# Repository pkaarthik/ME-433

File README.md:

# ME-433

This repo consists of assignments for the ME433 course at Northwestern University, offered in Spring 2021. Each of the individual folders has the submissions for those specific assignments (code, pictures and demo videos).

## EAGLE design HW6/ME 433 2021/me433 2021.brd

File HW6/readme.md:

**HW6**

In this assignment, I use Eagle CAD (free version) to design a circuit diagram, and it's PCB for the final project system in ME 433.

Note: Please find screenshots of the board, cropped for a more zoomed in view and a more full view. 

Note: The PololuDVR8835 uses a DIL-14 footprint despite not exactly matching the same footprint, since the pin spacing and column width of the DVR8835 matches a DIL14 footprint layout.

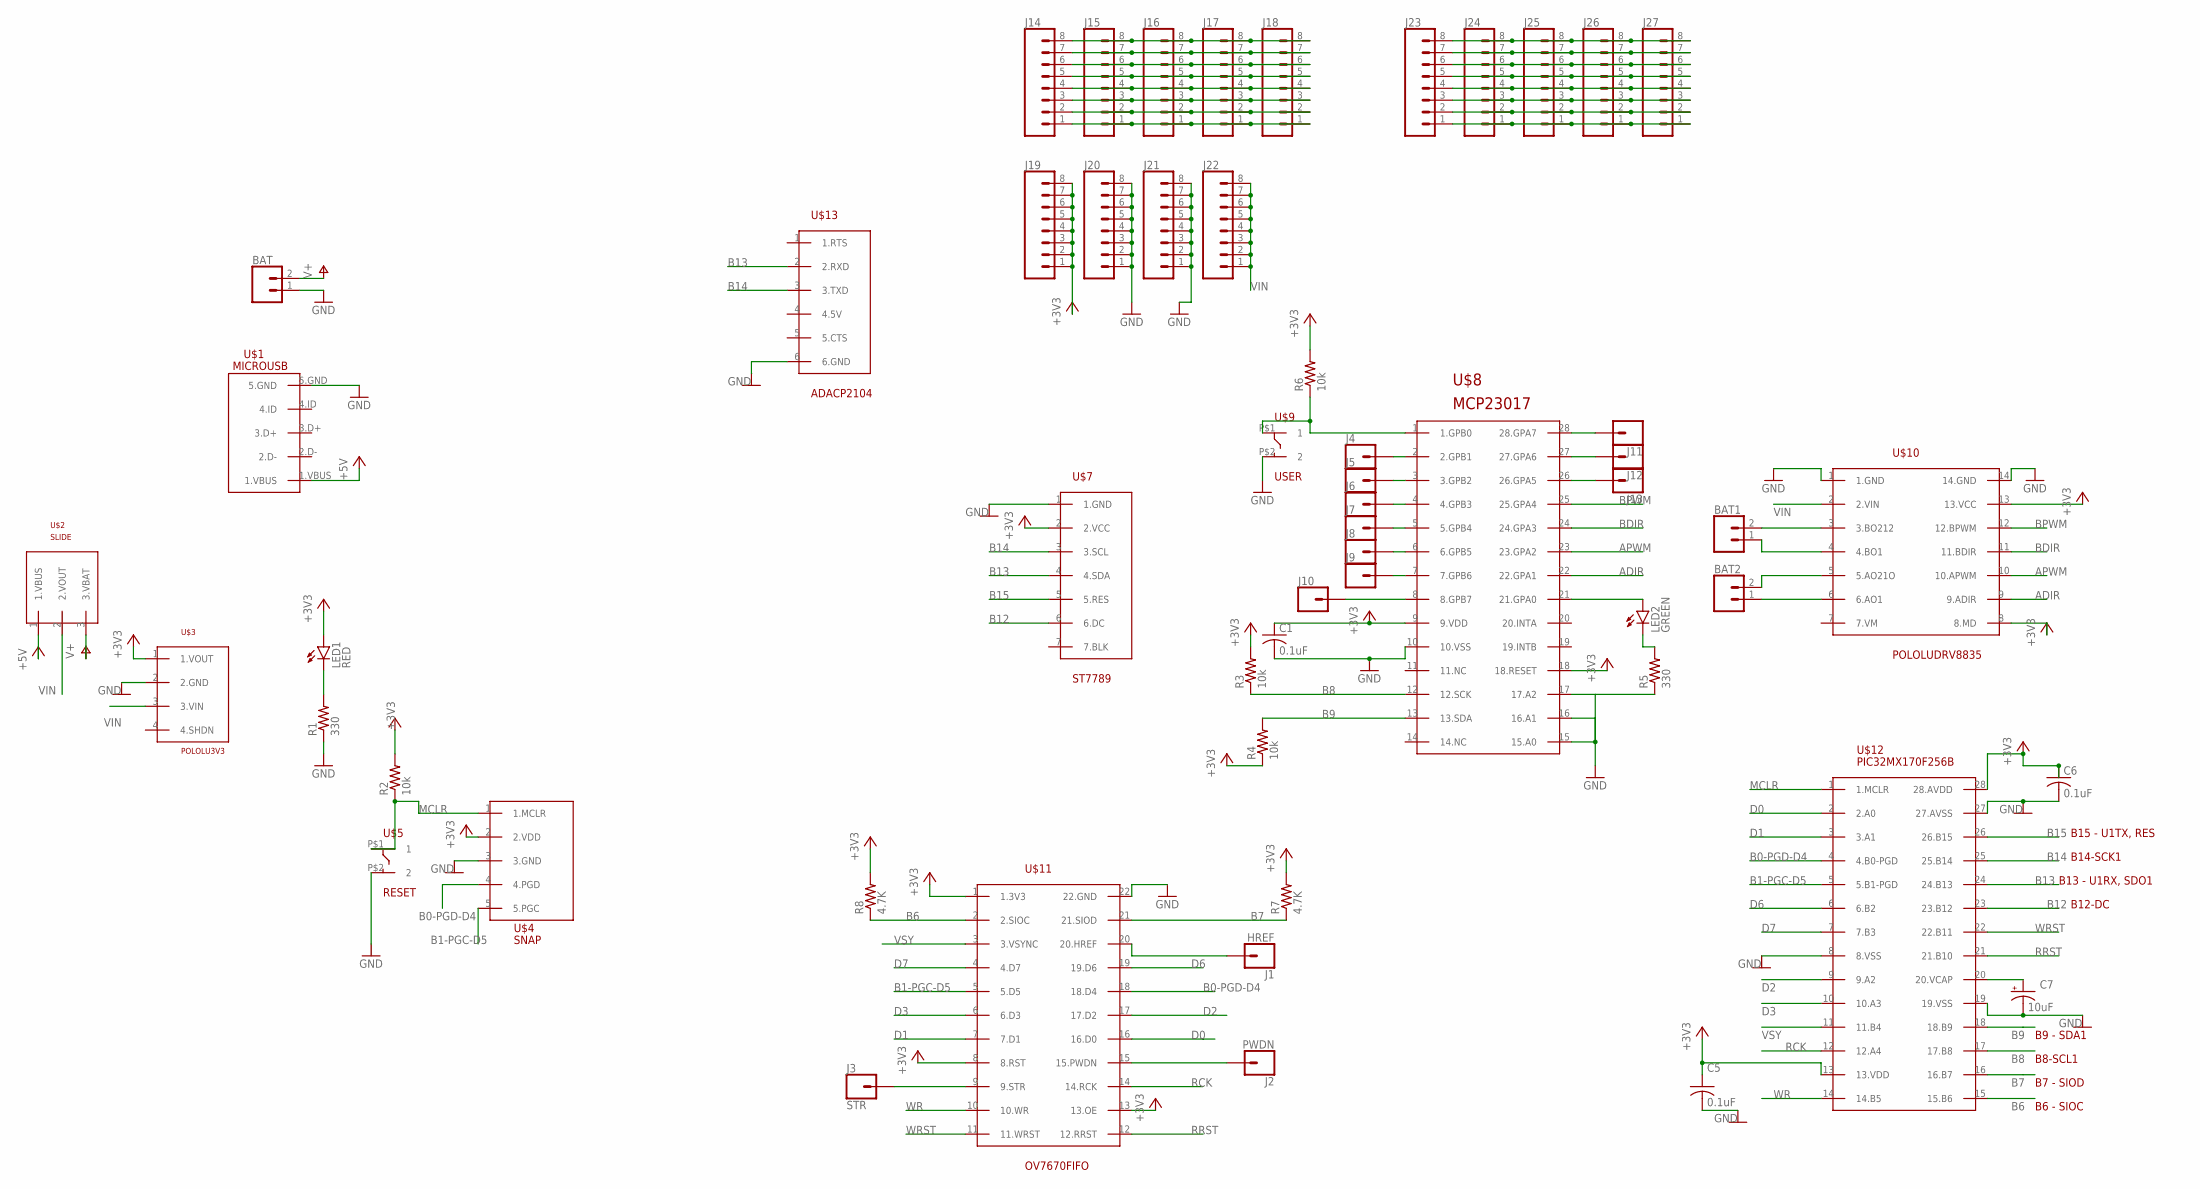
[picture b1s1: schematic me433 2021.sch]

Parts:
BAT, BAT1, BAT2: CONN_02; 1X02
C1, C5, C6: 0.1uF; C025-030X050
C7: 10uF; B45181B
J1: HREF; 1X01
J2: PWDN; 1X01
J3: STR; 1X01
J4, J5, J6, J7, J8, J9, J10, J11, J12, J13: CONN_01; 1X01
J14, J15, J16, J17, J18, J19, J20, J21, J22, J23, J24, J25, J26, J27: CONN_08"; 1X08
LED1: RED; LED3MM
LED2: GREEN; LED3MM
R1, R5: 330; 0207/10
R2, R3, R4, R6: 10k; 0207/10
R7, R8: 4.7K; 0207/10
U$1: MICROUSB
U$2: SLIDE
U$3: POLOLU3V3
U$4: SNAP
U$5: RESET; PUSH
U$7: ST7789
U$8: MCP23017; DIL28-3
U$9: USER; PUSH
U$10: POLOLUDRV8835; DIL14
U$11: OV7670FIFO
U$12: PIC32MX170F256B; DIL28-3
U$13: ADACP2104

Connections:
+3V3: C1.1, C5.1, C6.1, J19.1, J19.2, J19.3, J19.4, J19.5, J19.6, J19.7, J19.8, LED1.A, R2.2, R3.2, R4.1, R6.2, R7.2, R8.2, U$3.1 (1.VOUT), U$4.2 (2.VDD), U$7.2 (2.VCC), U$8.9 (9.VDD), U$8.18 (18.RESET), U$10.8 (8.MD), U$10.13 (13.VCC), U$11.1 (1.3V3), U$11.8 (8.RST), U$11.13 (13.OE), U$12.13 (13.VDD), U$12.28 (28.AVDD)
+5V: U$1.1.VBUS, U$2.1 (1.VBUS)
ADIR: U$8.22 (22.GPA1), U$10.9 (9.ADIR)
APWM: U$8.23 (23.GPA2), U$10.10 (10.APWM)
B0-PGD-D4: U$4.4 (4.PGD), U$11.18 (18.D4), U$12.4 (4.B0-PGD)
B1-PGC-D5: U$4.5 (5.PGC), U$11.5 (5.D5), U$12.5 (5.B1-PGD)
B6: R8.1, U$11.2 (2.SIOC), U$12.15 (15.B6)
B7: R7.1, U$11.21 (21.SIOD), U$12.16 (16.B7)
B8: R3.1, U$8.12 (12.SCK), U$12.17 (17.B8)
B9: R4.2, U$8.13 (13.SDA), U$12.18 (18.B9)
B12: U$7.6 (6.DC), U$12.23 (23.B12)
B13: U$7.4 (4.SDA), U$12.24 (24.B13), U$13.2 (2.RXD)
B14: U$7.3 (3.SCL), U$12.25 (25.B14), U$13.3 (3.TXD)
B15: U$7.5 (5.RES), U$12.26 (26.B15)
BDIR: U$8.24 (24.GPA3), U$10.11 (11.BDIR)
BPWM: U$8.25 (25.GPA4), U$10.12 (12.BPWM)
D0: U$11.16 (16.D0), U$12.2 (2.A0)
D1: U$11.7 (7.D1), U$12.3 (3.A1)
D2: U$11.17 (17.D2), U$12.9 (9.A2)
D3: U$11.6 (6.D3), U$12.10 (10.A3)
D6: U$11.19 (19.D6), U$12.6 (6.B2)
D7: U$11.4 (4.D7), U$12.7 (7.B3)
GND: BAT.1, C1.2, C5.2, C6.2, C7.-, J20.1, J20.2, J20.3, J20.4, J20.5, J20.6, J20.7, J20.8, J21.1, J21.2, J21.3, J21.4, J21.5, J21.6, J21.7, J21.8, R1.1, R5.1, U$1.5.GND, U$3.2 (2.GND), U$4.3 (3.GND), U$5.P$2 (2), U$7.1 (1.GND), U$8.10 (10.VSS), U$8.15 (15.A0), U$8.16 (16.A1), U$8.17 (17.A2), U$9.P$2 (2), U$10.1 (1.GND), U$10.14 (14.GND), U$11.22 (22.GND), U$12.8 (8.VSS), U$12.19 (19.VSS), U$12.27 (27.AVSS), U$13.6 (6.GND)
MCLR: R2.1, U$4.1 (1.MCLR), U$5.P$1 (1), U$12.1 (1.MCLR)
unnamed: LED1.K (C), R1.2
unnamed: J3.1, U$11.9 (9.STR)
unnamed: R6.1, U$8.1 (1.GPB0), U$9.P$1 (1)
unnamed: LED2.A, U$8.21 (21.GPA0)
unnamed: LED2.K (C), R5.2
unnamed: BAT1.2, U$10.3 (3.BO212)
unnamed: BAT1.1, U$10.4 (4.BO1)
unnamed: BAT2.2, U$10.5 (5.AO21O)
unnamed: BAT2.1, U$10.6 (6.AO1)
unnamed: J2.1, U$11.15 (15.PWDN)
unnamed: J1.1, U$11.20 (20.HREF)
unnamed: J4.1, U$8.2 (2.GPB1)
unnamed: J10.1, U$8.8 (8.GPB7)
unnamed: J5.1, U$8.3 (3.GPB2)
unnamed: J6.1, U$8.4 (4.GPB3)
unnamed: J7.1, U$8.5 (5.GPB4)
unnamed: C7.+, U$12.20 (20.VCAP)
unnamed: J8.1, U$8.6 (6.GPB5)
unnamed: J9.1, U$8.7 (7.GPB6)
unnamed: J11.1, U$8.28 (28.GPA7)
unnamed: J12.1, U$8.27 (27.GPA6)
unnamed: J13.1, U$8.26 (26.GPA5)
unnamed: J14.8, J15.8, J16.8, J17.8, J18.8
unnamed: J14.7, J15.7, J16.7, J17.7, J18.7
unnamed: J14.6, J15.6, J16.6, J17.6, J18.6
unnamed: J14.5, J15.5, J16.5, J17.5, J18.5
unnamed: J14.4, J15.4, J16.4, J17.4, J18.4
unnamed: J14.3, J15.3, J16.3, J17.3, J18.3
unnamed: J14.2, J15.2, J16.2, J17.2, J18.2
unnamed: J14.1, J15.1, J16.1, J17.1, J18.1
unnamed: J23.8, J24.8, J25.8, J26.8, J27.8
unnamed: J23.7, J24.7, J25.7, J26.7, J27.7
unnamed: J23.6, J24.6, J25.6, J26.6, J27.6
unnamed: J23.5, J24.5, J25.5, J26.5, J27.5
unnamed: J23.4, J24.4, J25.4, J26.4, J27.4
unnamed: J23.3, J24.3, J25.3, J26.3, J27.3
unnamed: J23.2, J24.2, J25.2, J26.2, J27.2
unnamed: J23.1, J24.1, J25.1, J26.1, J27.1
RCK: U$11.14 (14.RCK), U$12.12 (12.A4)
RRST: U$11.12 (12.RRST), U$12.21 (21.B10)
V+: BAT.2, U$2.3 (3.VBAT)
VIN: J22.1, J22.2, J22.3, J22.4, J22.5, J22.6, J22.7, J22.8, U$2.2 (2.VOUT), U$3.3 (3.VIN), U$10.2 (2.VIN)
VSY: U$11.3 (3.VSYNC), U$12.11 (11.B4)
WR: U$11.10 (10.WR), U$12.14 (14.B5)
WRST: U$11.11 (11.WRST), U$12.22 (22.B11)

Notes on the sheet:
B15 - U1TX, RES
B13 - U1RX, SDO1
B14-SCK1
B12-DC
B9 - SDA1
B8-SCL1
B7 - SIOD
B6 - SIOC

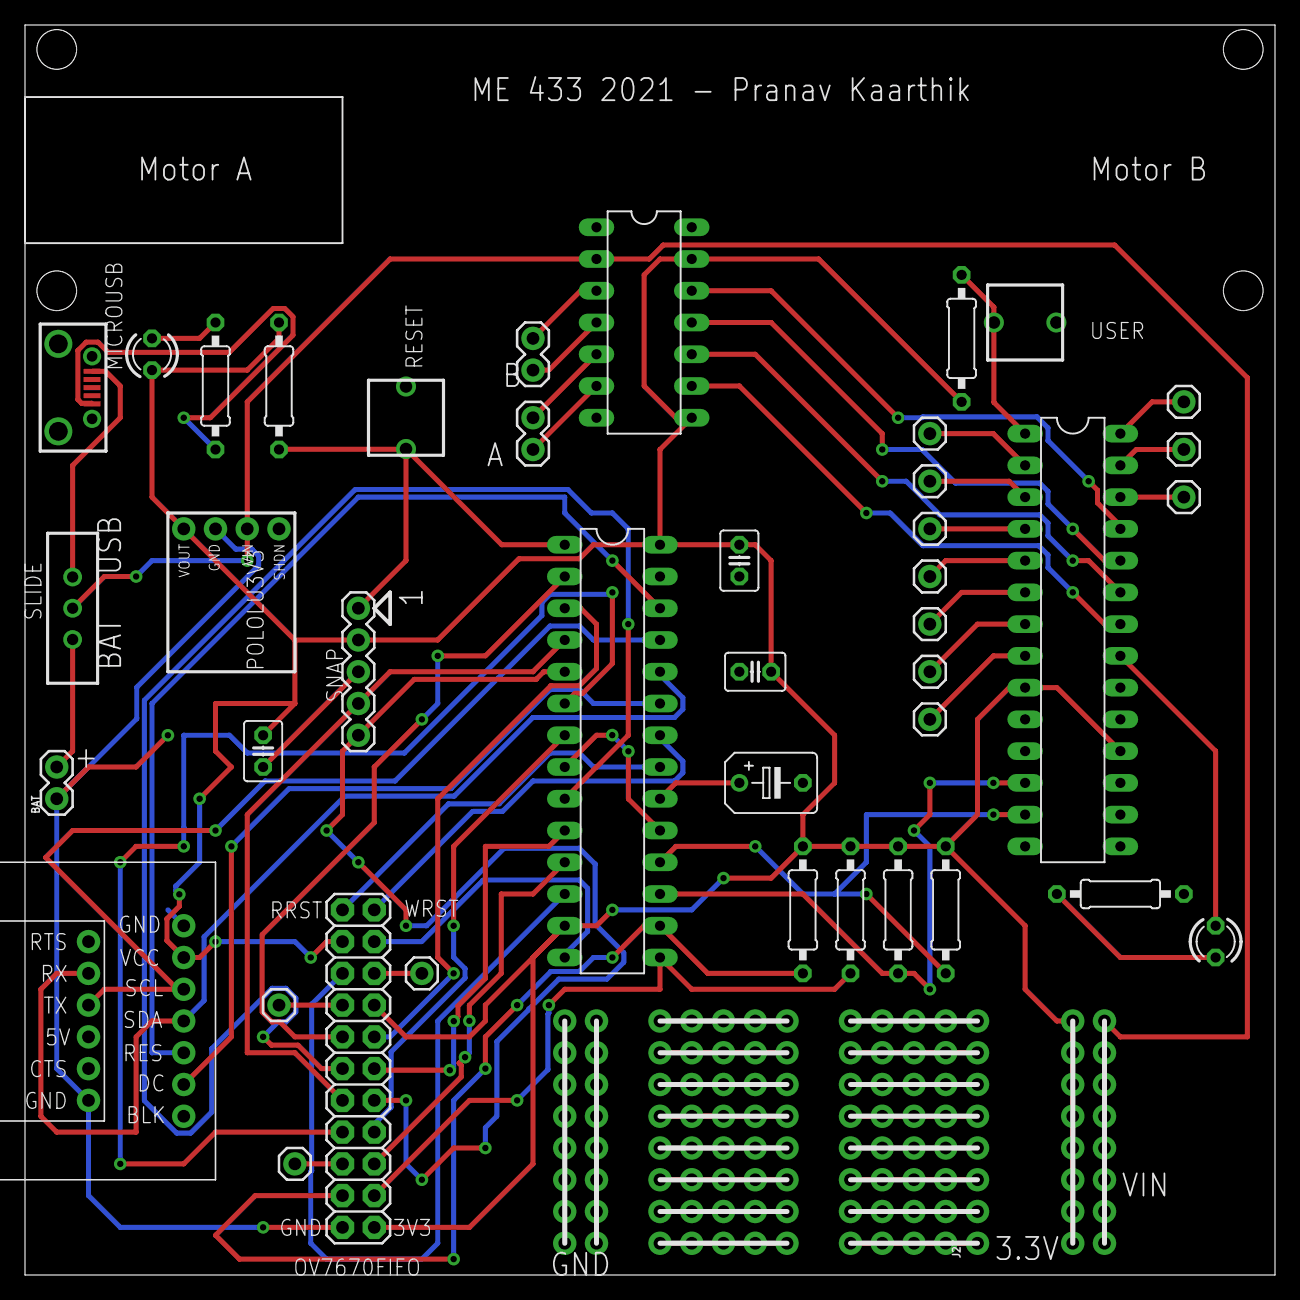
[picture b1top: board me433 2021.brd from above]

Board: 2 copper layers, 100.0 x 100.0 mm, 56 parts (0 on the bottom side), 69 nets.

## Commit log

2021-06-13 HW2 files
2022-02-15 HW4
    Uploading HW4
2022-02-16 HW5
    HW5
2022-02-16 HW7
    HW7
2022-02-17 HW8
    HW8
2022-02-18 HW9
    HW9
2022-02-18 HW10
    HW10
2022-02-18 Update HW10
2022-02-18 HW10
2022-02-20 HW11
    HW11
2022-02-21 HW6
    HW6
2022-02-21 Update Gerbers
2022-02-21 Update HW6
